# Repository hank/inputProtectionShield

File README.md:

# inputProtectionShield

The [JTAGULATOR](http://www.grandideastudio.com/portfolio/jtagulator/) took an existing project, the [JTAGENUM](https://github.com/cyphunk/JTAGenum), and reinvented the wheel in a few places. JTAGENUM runs on Arduino, and so this shield provides the Arduino Nano with the exact same hardware capabilities as the JTAGULATOR without the [hefty ($170 for a kit) price tag](https://hackerwarehouse.com/product/jtagulator/).

These hardware capabilities include:

* Input level conversion, including a range from 1.8-5v logic (larger range than JTAGulator)
* Input protection with current limiting and Schottky diode array

## Board

|                                      |                                           |
| ------------------------------------ | ----------------------------------------- |
|  |  |

## Bill Of Materials

* If the HSMS-285R is unavailable, the following parts should work:
  * [NUP4302MR6](http://www.mouser.com/ds/2/308/NUP4302MR6-99757.pdf)
  * [TESD5V0V4UCU6 RFG](www.taiwansemi.com/products/datasheet/TESD5V0V4UCU6_A1705.pdf) (Bought 12 for $4.13, 4x for $1.37)
* MOSFETs: [50pcs BSS138  MOSFET N-CH 50V .22 AMP IN SOT-23 PKG. USA SUPPLIER](http://www.ebay.com/itm/382540619634) ($3.25, $0.065 each, 8x for $0.52)
* Resistors:
  * [Lot of 125 CRCW04021K00FKTD Vishay Chip Resistor 1k Ohm 62.5mW 1/16W 1% 0402 NOS](http://www.ebay.com/itm/201820263322) ($3.99, $0.03192 each, 16x for $0.51)
  * [Lot of 75 RK73H1ELTP1002F KOA Chip Resistor 10k Ohm 100mW 1/10W 1% 0402 NOS](http://www.ebay.com/itm/201683750387) ($5.40, $0.072 each, 8x for $0.57)
* Arduino: [Arduino Nano V3.0 ATmega328 5V Micro-controller CH340E](http://www.ebay.com/itm/391965564336) ($11.50)
* Boards: 6 for $13.40 from OSHPark, $2.23 each

**Total: $16.70** per unit

| **Part**          | **Value**    | **Device**         | **Package** | **Description**                                            |
| ----------------- | ------------ | ------------------ | ----------- | ---------------------------------------------------------- |
| D1-D4 (4x)        | HSMS-285R    | HSMS-285R          | SOT363      | Surface Mount Microwave Schottky Detector Diodes Ring Quad |
| Q1-Q8 (8x)        | BSS138       | MOSFET-NCHANNELSMD | SOT23-3     | BSS138 MOSFET                                              |
| R1-R15, R17 (16x) | 10k          | R-US_R0402         | R0402       | RESISTOR, American symbol                                  |
| R16, R18-R24 (8x) | 1k           | R-US_R0402         | R0402       | RESISTOR, American symbol                                  |
| SV1               |              | FE15-1             | FE15        | FEMALE HEADER                                              |
| SV2               |              | FE15-1             | FE15        | FEMALE HEADER                                              |
| SV3               |              | MA03-1             | MA03-1      | PIN HEADER                                                 |
|                   | ARDUINO NANO | ARDUINO NANO       | PDIP-32     | Arduino Nano                                               |

## Credits

* [JTAGulator Versus JTAGENUM Blog Post](https://p16.praetorian.com/blog/jtagulator-vs-jtagenum-tools-for-identifying-jtag-pins-in-iot-devices) and original board design by Dylan Ayrey. Great work!
* Board layout tweaks (so far just the silkscreening fonts and other aesthetic tweaks) by Erik Gregg

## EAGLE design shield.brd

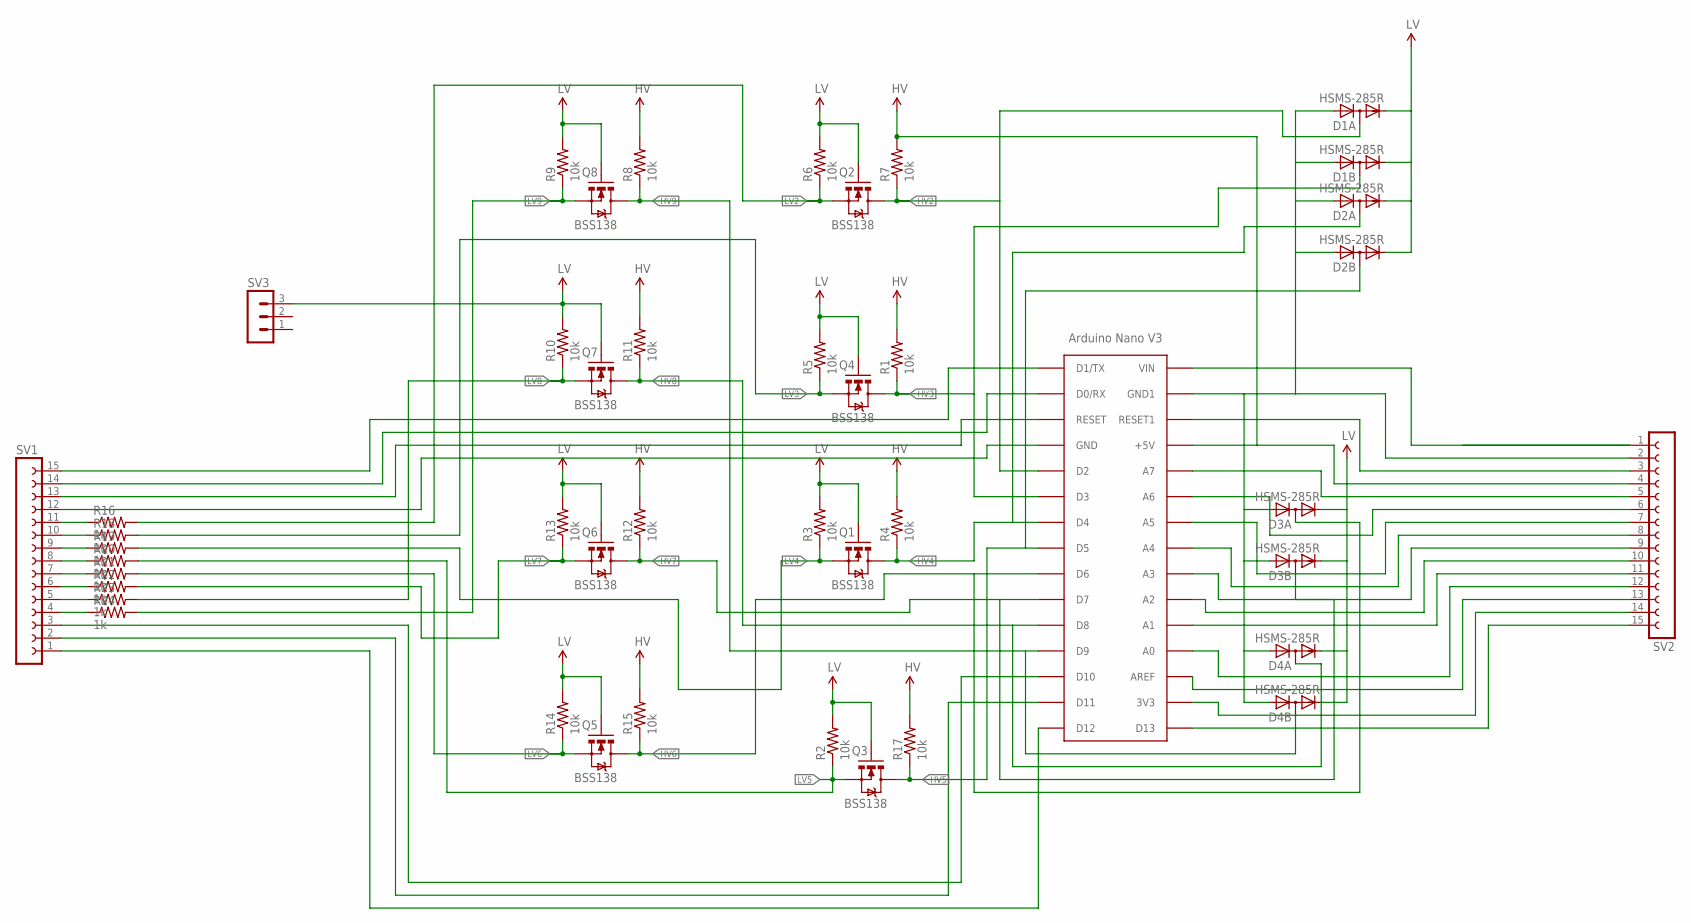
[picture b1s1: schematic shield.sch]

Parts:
D1, D2, D3, D4: HSMS-285R; SOT363
Q1, Q2, Q3, Q4, Q5, Q6, Q7, Q8: BSS138; SOT23-3
R1, R2, R3, R4, R5, R6, R7, R8, R9, R10, R11, R12, R13, R14, R15, R17: 10k; R0402
R16, R18, R19, R20, R21, R22, R23, R24: 1k; R0402
SV1, SV2: FE15-1; FE15
SV3: MA03-1
U$1: ARDUINONANO; PDIP-32

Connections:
HV: R1.2, R4.2, R7.2, R8.2, R11.2, R12.2, R15.2, R17.2, SV2.4, U$1.+5V
HV2: D1.2 (AC), Q2.3 (D), R7.1, U$1.D2
HV3: D1.5 (AC), Q4.3 (D), R1.1, U$1.D3
HV4: D2.2 (AC), Q1.3 (D), R4.1, U$1.D4
HV5: D2.5 (AC), Q3.3 (D), R17.1, U$1.D5
HV6: D3.2 (AC), Q5.3 (D), R15.1, U$1.D6
HV7: D3.5 (AC), Q6.3 (D), R12.1, U$1.D7
HV8: D4.2 (AC), Q7.3 (D), R11.1, U$1.D8
HV9: D4.5 (AC), Q8.3 (D), R8.1, U$1.D9
LV: D1.1 (C), D1.4 (C), D2.1 (C), D2.4 (C), D3.1 (C), D3.4 (C), D4.1 (C), D4.4 (C), Q1.1 (G), Q2.1 (G), Q3.1 (G), Q4.1 (G), Q5.1 (G), Q6.1 (G), Q7.1 (G), Q8.1 (G), R2.2, R3.2, R5.2, R6.2, R9.2, R10.2, R13.2, R14.2, SV3.3
LV2: Q2.2 (S), R6.1, R16.2
LV3: Q4.2 (S), R5.1, R18.2
LV4: Q1.2 (S), R3.1, R19.2
LV5: Q3.2 (S), R2.1, R20.2
LV6: Q5.2 (S), R14.1, R21.2
LV7: Q6.2 (S), R13.1, R22.2
LV8: Q7.2 (S), R10.1, R23.2
LV9: Q8.2 (S), R9.1, R24.2
unnamed: D1.3 (A), D1.6 (A), D2.3 (A), D2.6 (A), D3.3 (A), D3.6 (A), D4.3 (A), D4.6 (A), SV2.2, U$1.GND1
unnamed: SV2.9, U$1.A4 (A3)
unnamed: SV2.10, U$1.A5 (A2)
unnamed: SV2.11, U$1.A6 (A1)
unnamed: SV2.12, U$1.A7 (A0)
unnamed: SV2.13, U$1.AREF
unnamed: SV2.14, U$1.3V3
unnamed: SV2.15, U$1.D13
unnamed: SV2.8, U$1.A3 (A4)
unnamed: SV2.7, U$1.A2 (A5)
unnamed: SV2.6, U$1.A1 (A6)
unnamed: SV2.5, U$1.A0 (A7)
unnamed: R16.1, SV1.11
unnamed: SV2.3, U$1.RESET1
unnamed: SV2.1, U$1.VIN
unnamed: SV1.15, U$1.D1/TX
unnamed: SV1.14, U$1.D0/RX
unnamed: SV1.13, U$1.RESET
unnamed: SV1.12, U$1.GND
unnamed: R18.1, SV1.10
unnamed: R19.1, SV1.9
unnamed: R20.1, SV1.8
unnamed: R21.1, SV1.7
unnamed: R22.1, SV1.6
unnamed: R23.1, SV1.5
unnamed: R24.1, SV1.4
unnamed: SV1.3, U$1.D10
unnamed: SV1.2, U$1.D11
unnamed: SV1.1, U$1.D12

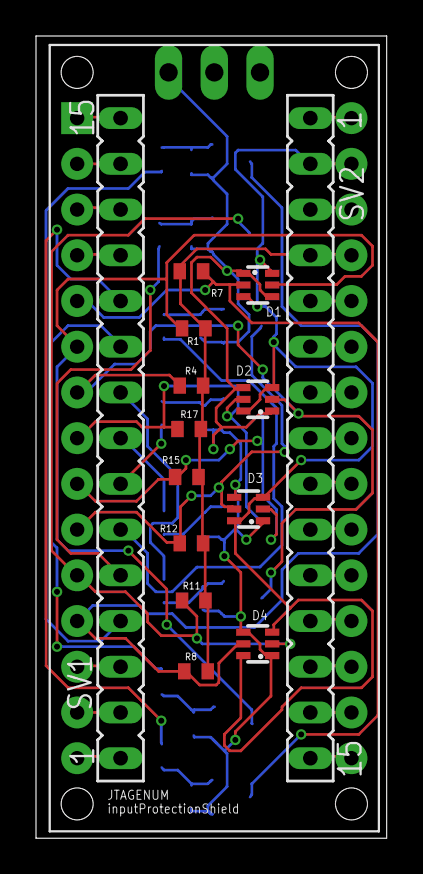
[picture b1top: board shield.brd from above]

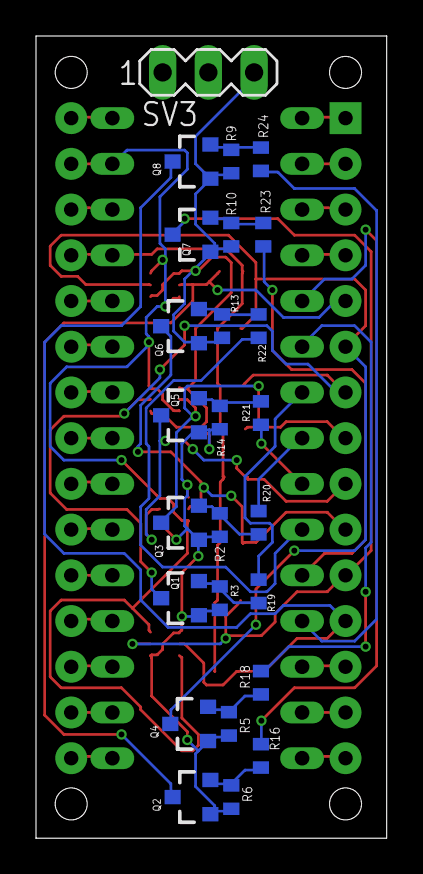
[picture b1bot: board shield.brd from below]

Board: 2 copper layers, 19.5 x 44.6 mm, 40 parts (25 on the bottom side), 47 nets.

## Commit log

2016-03-06 adding shield schematic and board designs
2016-03-06 updating readme
2016-03-06 fixing ground line
2016-03-06 optimizing board layout using reverse side for mounting
2016-03-07 reducing size dramatically
2018-08-26 Adding silk name
    Adding a silked name of the board so I don't forget what it is.
2018-08-26 More updates, ordered boards
2018-08-28 Updating Docs
    Adding docs with BOM, better pictures, etc.
